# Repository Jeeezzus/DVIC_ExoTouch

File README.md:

# ExoTouch - DIY VR Haptic Glove

ExoTouch is an open-source project aimed at developing a DIY VR haptic glove that provides a realistic sense of touch for virtual reality experiences. This repository contains the hardware and software designs for several prototypes of the ExoTouch glove.

## Overview

We have produced several versions of the ExoTouch glove, each with different architectures and features, based on the  Lucid Glove: a cheap VR haptic glove that only requires potentiometers, servo motors, strings, and an ESP. It was designed By Lucas VRTech (all credits to https://github.com/LucidVR/lucidgloves)

The ExoTouch V1 is based on a three-piece exoskeleton that pulls a toothed bar that a servo-motor can lock to provide haptic feedback. The system was enhanced with a rudimentary PCB to control the servo motors and send the potentiometer information to the computer.

ExoTouch V2 was a prototype using a semi-rigid tube to connect the front of the finger to the potentiometer. However, this design was not promising and was quickly abandoned.

Finally, ExoTouch V3 is the latest version of the glove, based on the work of Nick Iacobbo. This exoskeleton follows each phalange of the hand, allowing much more efficient tracking of the position of the fingers. The potentiometers have been mounted on the back of the hand, offering better wrist flexibility. A rudimentary PCB has been added to send the potentiometer values to the computer, using an ESP32-based MCU board. This board includes a charge controller, allowing a battery to be directly connected to the ESP, making the glove wireless.

## Force Feedback System

The ExoTouch V3 introduced a new force feedback system, similar to bike brakes. Two brake plates are pressed against the potentiometer's moving part, introducing a friction force that blocks the fingers. Although the force feedback system is not as powerful as some commercial haptic gloves, it provides a realistic sense of touch for VR experiences.

## Limitations and Future Work

The ExoTouch gloves still have some limitations, including the force feedback system not being as strong as commercial gloves, the need to place the controller at the back of the hand, and the volume of the glove being a bit too large. However, we believe that this project can be improved by developing more powerful force feedback systems, improving the glove design, exploring alternative control mechanisms, and conducting further user studies to better understand the needs of different user groups.

## Conclusion

ExoTouch is a DIY VR haptic glove project that aims to provide a more immersive virtual reality experience. By sharing our designs and code, we hope to encourage others to experiment and improve upon our work. We welcome feedback, contributions, and collaborations from the community.

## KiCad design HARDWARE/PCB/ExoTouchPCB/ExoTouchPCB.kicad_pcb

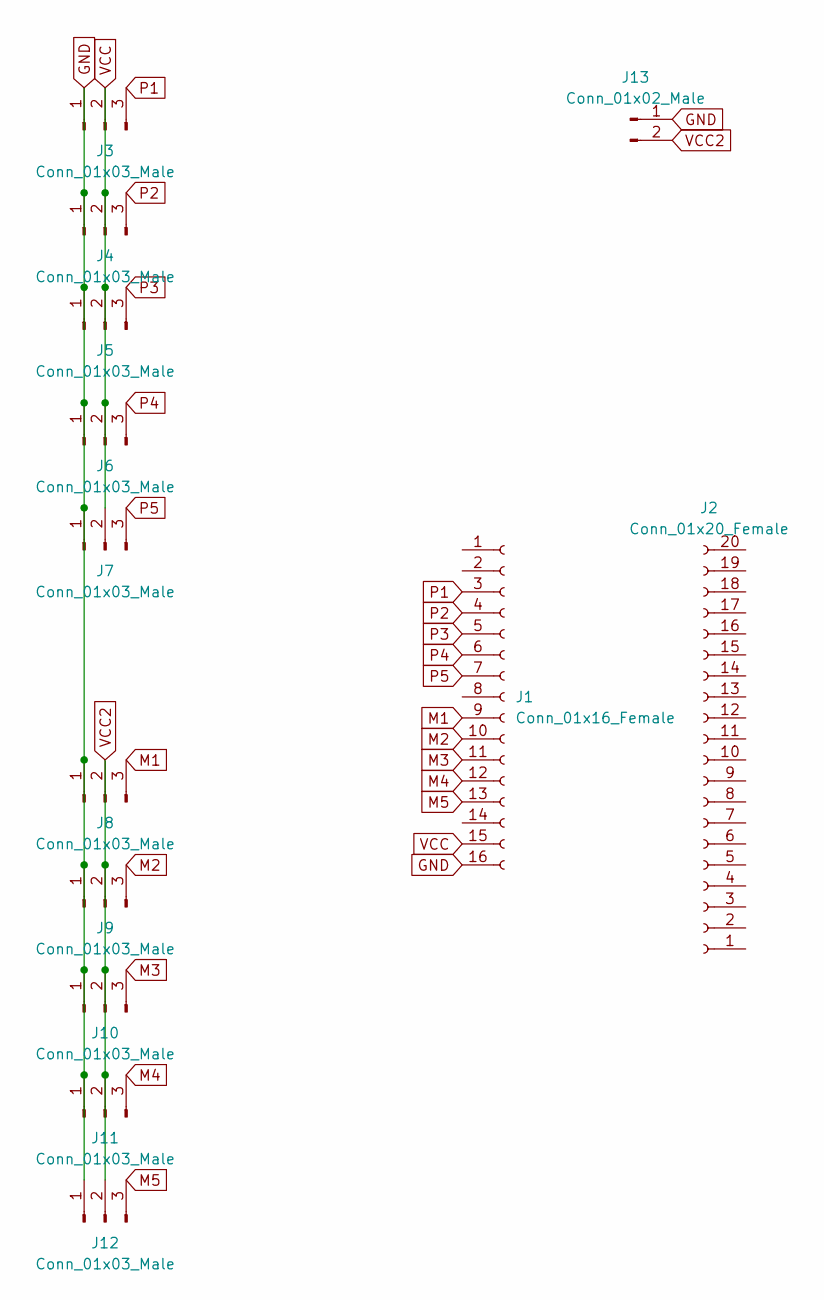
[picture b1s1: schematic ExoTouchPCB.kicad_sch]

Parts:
J1: Conn_01x16_Female; PinHeader_1x16_P2.54mm_Vertical
J2: Conn_01x20_Female; PinHeader_1x20_P2.54mm_Vertical
J3, J4, J5, J6, J7, J8, J9, J10, J11, J12: Conn_01x03_Male; PinHeader_1x03_P2.54mm_Vertical
J13: Conn_01x02_Male; PinHeader_1x02_P2.54mm_Vertical

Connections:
GND: J1.16, J3.1, J4.1, J5.1, J6.1, J7.1, J8.1, J9.1, J10.1, J11.1, J12.1, J13.1
M1: J1.9, J8.3
M2: J1.10, J9.3
M3: J1.11, J10.3
M4: J1.12, J11.3
M5: J1.13, J12.3
P1: J1.3, J3.3
P2: J1.4, J4.3
P3: J1.5, J5.3
P4: J1.6, J6.3
P5: J1.7, J7.3
VCC: J1.15, J3.2, J4.2, J5.2, J6.2, J7.2
VCC2: J8.2, J9.2, J10.2, J11.2, J12.2, J13.2

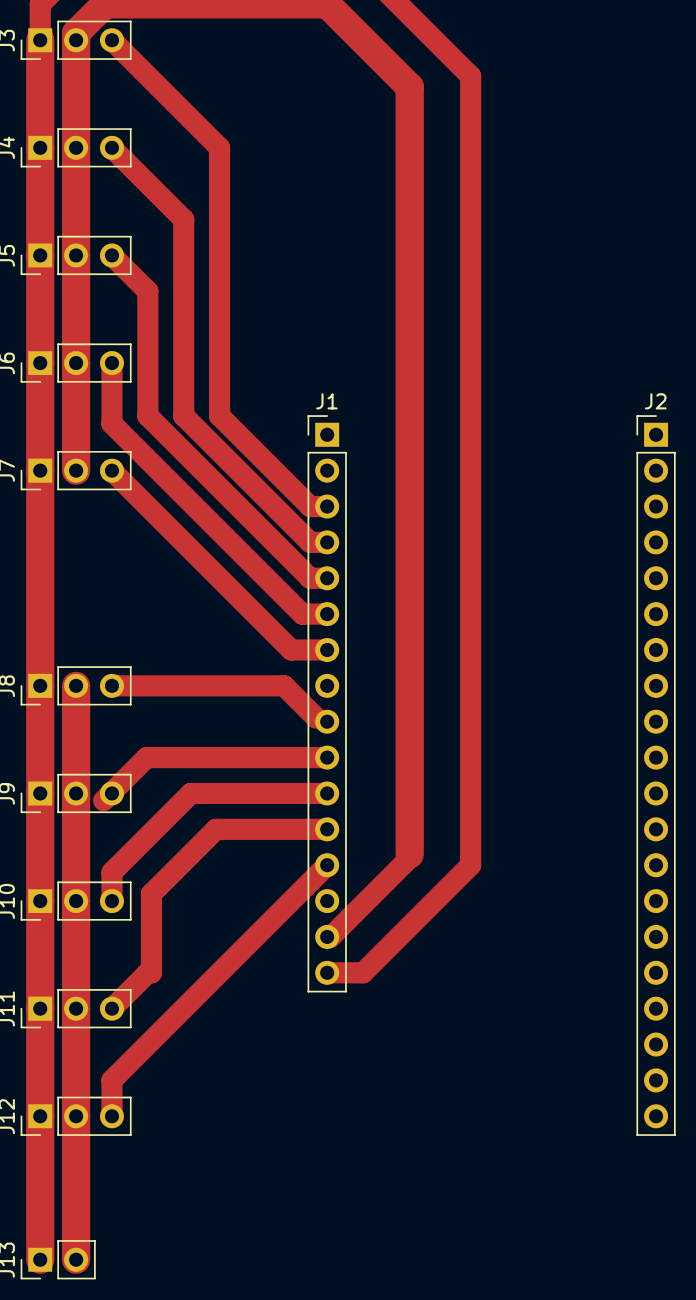
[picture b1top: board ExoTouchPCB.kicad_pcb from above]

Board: 2 copper layers, 13 parts (0 on the bottom side), 13 nets.

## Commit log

2023-03-03 Reorganized
2023-03-03 Pictures, firmware
2023-03-03 FIRMWARE
2023-03-24 Gitignore
2023-03-24 gitignred2
2023-03-24 Exotouch V3 updated
